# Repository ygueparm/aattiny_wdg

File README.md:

# Another ATtiny85 Watchdog for ESP32

Ce projet fournit un **watchdog externe** pour ESP32, compatible avec **Arduino IDE 2.x**.

---

## 🔧 Code à inclure dans votre projet ESP32

```cpp
#define WATCHDOG_EXT         25 // IO ESP32

// Configuration du watchdog
extern bool watchdogState;
extern unsigned long previousMillisWD;
extern const long intervalWD;

void setup() {
  unsigned long previousMillisWD = 0; 
const long intervalWD = 200;  //clignotement 500 >1.6hz
bool watchdogState = true;
}

void loop() {
  // Watchdog externe créant un clignotement < 1.6 Hz
  unsigned long currentMillisWD = millis();

  if (currentMillisWD - previousMillisWD >= intervalWD) {
    previousMillisWD = currentMillisWD;
    watchdogState = !watchdogState;  // Inverse l'état
    digitalWrite(WATCHDOG_EXT, watchdogState);
  }

  // ... reste de votre code
}
```

---

# 🔌 Programmation ISP de l'ATtiny85

Pour programmer l'ATtiny85, vous devez utiliser **Arduino comme ISP**. NE SURTOUT PAS CONNECTEZ la carte a lesp32 pendant la programmation

brochage pour utiliser larduino uno comme programateur : 

'''
| Arduino Uno | ATtiny85 (broche physique) | Sérigraphie | Fonction |
| ----------- | -------------------------- | ----------- | -------- |
| **10**      | 1                          | **P5**      | RESET    |
| **11**      | 5                          | **P0**      | MOSI     |
| **12**      | 6                          | **P1**      | MISO     |
| **13**      | 7                          | **P2**      | SCK      |
| **5V**      | 8                          | **VCC**     | Alim +5V |
| **GND**     | 4                          | **GND**     | Masse    |
'''

## 1. Charger ArduinoISP

Dans l'IDE Arduino :

* *File > Examples > ArduinoISP*
* Téléversez sur votre Arduino UNO/Nano (le programmateur).

## 2. Ajouter la carte ATtiny85

* *File > Preferences*
* Dans **Additional board manager URLs**, ajoutez :

```
https://raw.githubusercontent.com/damellis/attiny/ide-1.6.x-boards-manager/package_damellis_attiny_index.json
```

Ensuite :

* *Tools > Board > Boards Manager*
* Recherchez **attiny** et installez.

## 3. Configuration

Dans *Tools* :

* **Board** : ATtiny85
* **Clock** : 1 MHz (interne)
* **Programmer** : Arduino as ISP

###  Première utilisation de l'ATtiny85

1. Ne soudez que l'ATtiny85 et les pins de programmation.
2. *Tools > Burn Bootloader* (installe les fuses corrects).
3. Votre ATtiny85 est maintenant prêt pour le projet.

 * fichier .ino >   aattiny_wdg/attiny_watchdog/attiny_watchdog.ino
 * vous pouvez soudez le reste des composants ! et le mettre en place
---

# 🏭 Production JLCPCB

Rendez-vous dans :

```
aattiny_wdg/attiny/production/
```

## ✔ Pour fabriquer uniquement le PCB

Utilisez **attiny.zip**, puis :

* envoyez-le sur JLCPCB ou PCBWay
* vous recevrez les PCB nus, à souder vous-même

## ✔ Pour la production complète (avec composants)

Les autres fichiers du dossier sont prévus pour l'assemblage automatisé.

---

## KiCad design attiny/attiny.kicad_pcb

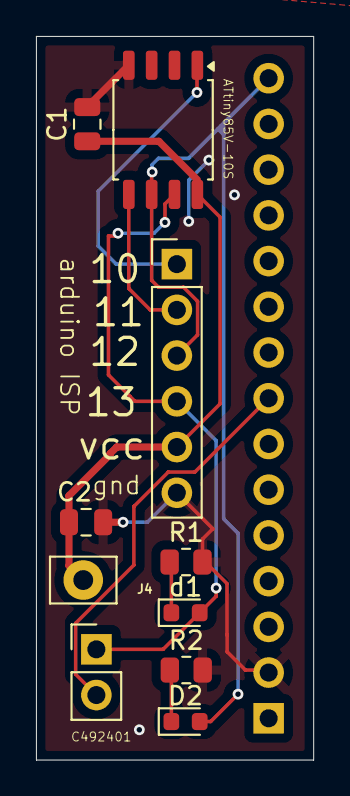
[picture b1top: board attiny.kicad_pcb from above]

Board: 2 copper layers, 15.4 x 40.2 mm, 11 parts (1 on the bottom side), 9 nets.

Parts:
C1, C2: 100nf_C49678; C_0805_2012Metric
D2: LED_C2286; LED_0603_1608Metric
J4: Conn_01x01; Pin_D1.1mm_L10.2mm_W3.5mm_Flat
R1, R2: 12kΩ_C17444; R_0805_2012Metric
U1: ATtiny85V-10S; SOIC-8_5.3x5.3mm_P1.27mm
arduino1: C492405; PinHeader_1x06_P2.54mm_Vertical
cavalier1: C492401; PinHeader_1x02_P2.54mm_Vertical
d1: LED_C2290; LED_0603_1608Metric
esp32: PinHeader_1x15_P2.54mm_Vertical

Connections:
GND: C1.2, C2.2, R1.2, R2.2, U1.4 (GND), arduino1.6, esp32.2
unnamed: D2.2 (A), U1.6 (PB1), arduino1.3, esp32.15
unnamed: D2.1 (K), R2.1
unnamed: U1.5 (AREF/PB0), arduino1.2
unnamed: U1.7 (PB2), arduino1.4, cavalier1.1, d1.2 (A)
unnamed: U1.1 (~RESET/PB5), arduino1.1
unnamed: cavalier1.2, esp32.8
unnamed: R1.1, d1.1 (K)
VCC: C1.1, C2.1, J4.1, U1.8 (VCC), arduino1.5

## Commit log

2025-11-18 Create test
2025-11-18 Description de vos modifications
2025-11-18 Ajout projet complet ATTiny WDG avec PCB, schematics et Gerbers
2025-11-18 Ajout du code arduino-ide pour l'attiny85
2025-11-18 nettoyage
2025-11-19 mise a jour readme
2025-11-19 fichier production jlcpcb
2025-11-19 mise en place license
2025-11-19 correction erreur serigraphie + nouveau fichier de production
2025-11-19 correction routage mineur
2025-11-19 composant basic pour jlpcb (très petit dificilement soudable a la main)
2025-11-19 mise a jour reference resistance avec ref jlcsc
2025-11-19 ajout configuration kicad ignore
2025-11-21 acomposant pour production automatique chez jlcpcb environ 18€ 2 pcb assemblé et 3 non assemblé
2025-11-22 mise a jour pcb
2025-12-08 ajout details readme
2025-12-08 correction code d'exemple
2025-12-12 Create LICENSE
2025-12-17 mise a jour readme tableau broche ISP
